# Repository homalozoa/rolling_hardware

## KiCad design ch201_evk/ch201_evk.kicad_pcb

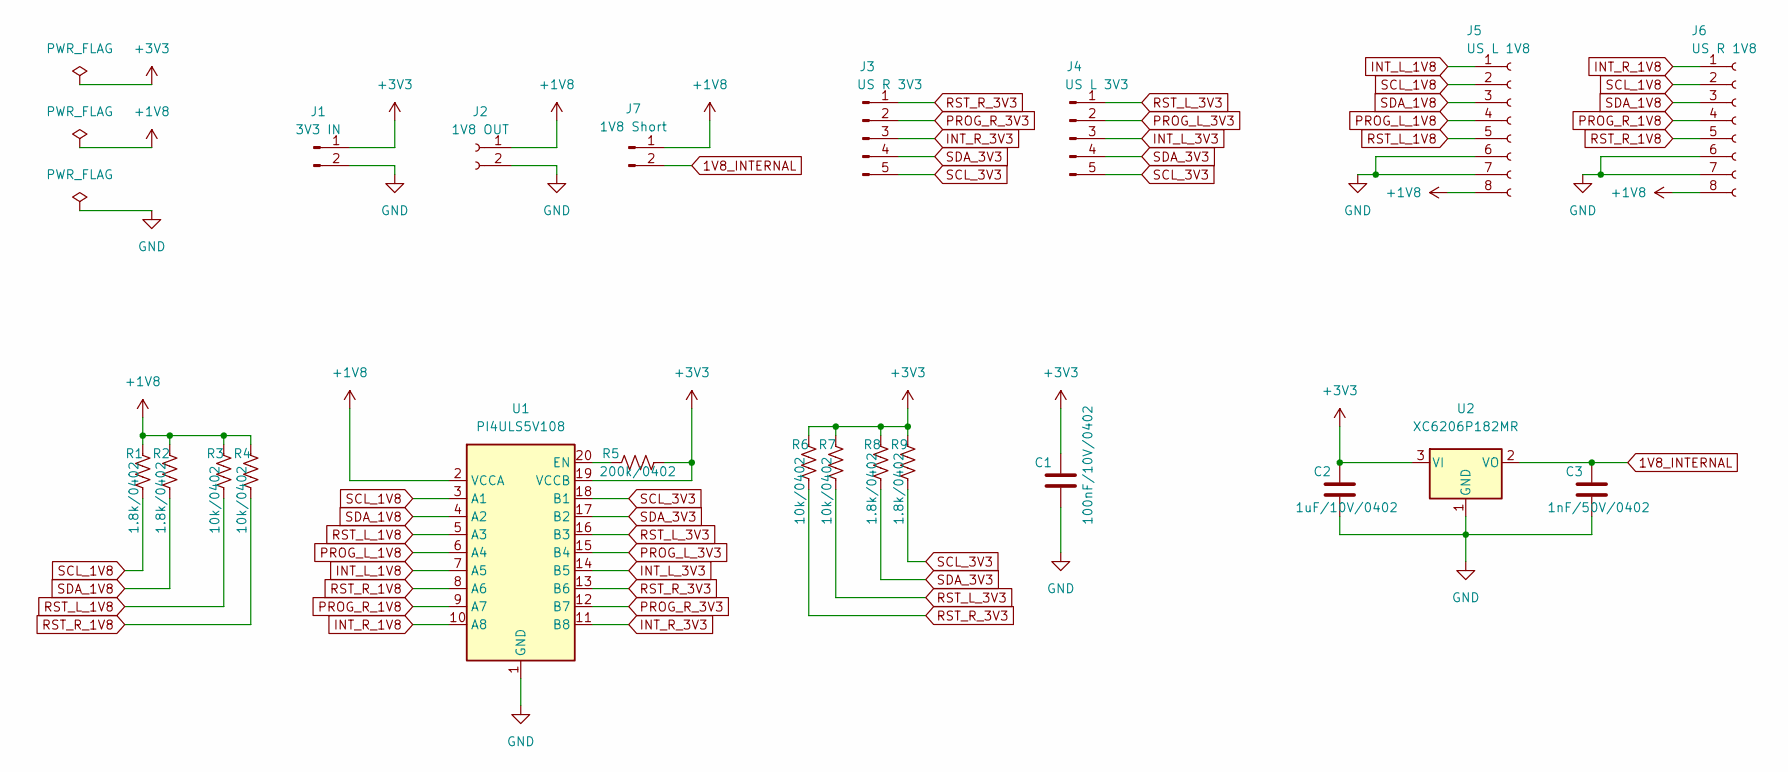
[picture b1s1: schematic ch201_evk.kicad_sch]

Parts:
C1: 100nF/10V/0402; C_0402_1005Metric
C2: 1uF/10V/0402; C_0402_1005Metric
C3: 1nF/50V/0402; C_0402_1005Metric
J1: 3V3 IN; PinHeader_1x02_P2.54mm_Vertical
J2: 1V8 OUT; PinHeader_1x02_P2.54mm_Vertical
J3: US R 3V3; PinHeader_1x05_P2.54mm_Vertical
J4: US L 3V3; PinHeader_1x05_P2.54mm_Vertical
J5: US L 1V8; MOLEX_5034800800
J6: US R 1V8; MOLEX_5034800800
J7: 1V8 Short; PinHeader_1x02_P2.54mm_Vertical
R1, R2, R8, R9: 1.8k/0402; R_0402_1005Metric
R3, R4, R6, R7: 10k/0402; R_0402_1005Metric
R5: 200k/0402; R_0402_1005Metric
U1: PI4ULS5V108; DHVQFN20_SOT764-1
U2: XC6206P182MR; SOT-23

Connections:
1V8_INTERNAL: C3.1, J7.2, U2.2 (VO)
+1V8: J2.1, J5.8, J6.8, J7.1, R1.1, R2.1, R3.1, R4.1, U1.2 (VCCA); also elsewhere on the board
+3V3: C1.1, C2.1, J1.1, R5.2, R6.1, R7.1, R8.1, R9.1, U1.19 (VCCB), U2.3 (VI)
GND: C1.2, C2.2, C3.2, J1.2, J2.2, J5.6, J5.7, J6.6, J6.7, U1.1 (GND), U2.1 (GND); also elsewhere on the board
INT_L_1V8: J5.1, U1.7 (A5); also elsewhere on the board
INT_L_3V3: J4.3, U1.14 (B5)
INT_R_1V8: J6.1, U1.10 (A8); also elsewhere on the board
INT_R_3V3: J3.3, U1.11 (B8)
unnamed: R5.1, U1.20 (EN)
PROG_L_1V8: J5.4, U1.6 (A4); also elsewhere on the board
PROG_L_3V3: J4.2, U1.15 (B4)
PROG_R_1V8: J6.4, U1.9 (A7); also elsewhere on the board
PROG_R_3V3: J3.2, U1.12 (B7)
RST_L_1V8: J5.5, R3.2, U1.5 (A3); also elsewhere on the board
RST_L_3V3: J4.1, R7.2, U1.16 (B3)
RST_R_1V8: J6.5, R4.2, U1.8 (A6); also elsewhere on the board
RST_R_3V3: J3.1, R6.2, U1.13 (B6)
SCL_1V8: J5.2, J6.2, R1.2, U1.3 (A1); also elsewhere on the board
SCL_3V3: J3.5, J4.5, R9.2, U1.18 (B1)
SDA_1V8: J5.3, J6.3, R2.2, U1.4 (A2); also elsewhere on the board
SDA_3V3: J3.4, J4.4, R8.2, U1.17 (B2)

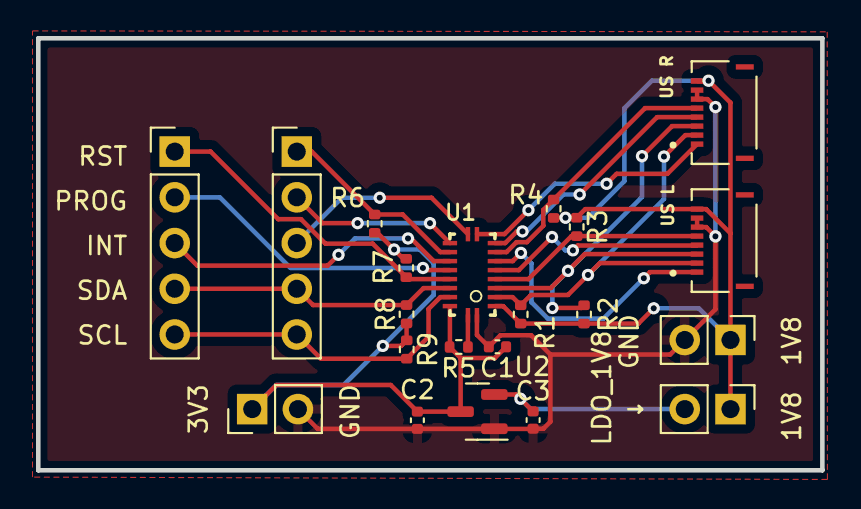
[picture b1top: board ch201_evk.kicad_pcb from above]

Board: 2 copper layers, 43.6 x 24.0 mm, 21 parts (0 on the bottom side), 21 nets.

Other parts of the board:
US L: US L 1V8; MOLEX_5034800800
US R: US R 1V8; MOLEX_5034800800

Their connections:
+1V8: US L.8, US R.8; also elsewhere on the board
GND: US L.6, US L.7, US R.6, US R.7; also elsewhere on the board
INT_L_1V8: US L.1; also elsewhere on the board
INT_R_1V8: US R.1; also elsewhere on the board
PROG_L_1V8: US L.4; also elsewhere on the board
PROG_R_1V8: US R.4; also elsewhere on the board
RST_L_1V8: US L.5; also elsewhere on the board
RST_R_1V8: US R.5; also elsewhere on the board
SCL_1V8: US L.2, US R.2; also elsewhere on the board
SDA_1V8: US L.3, US R.3; also elsewhere on the board

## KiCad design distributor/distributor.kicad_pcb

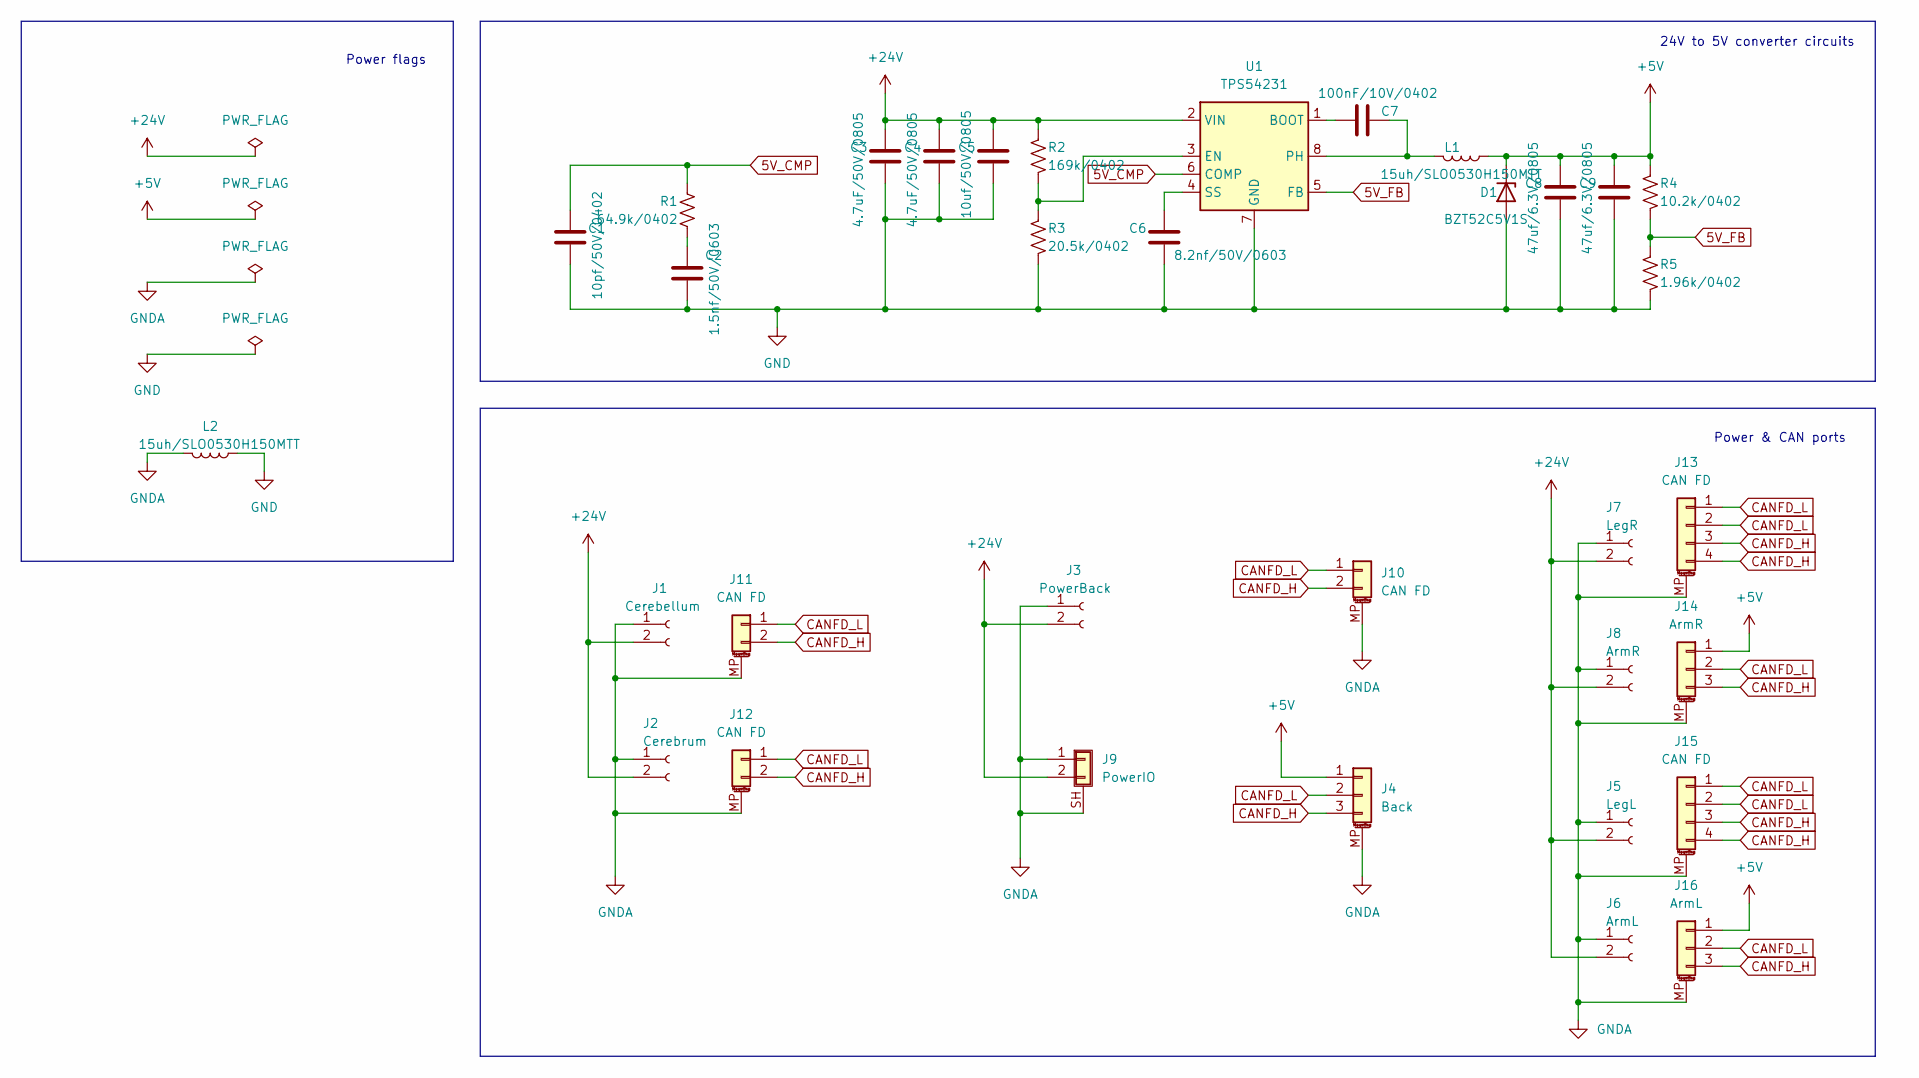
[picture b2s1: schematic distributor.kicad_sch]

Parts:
C1: 10pf/50V/0402; C_0402_1005Metric
C2: 1.5nf/50V/0603; C_0603_1608Metric
C3, C4: 4.7uF/50V/0805; C_0805_2012Metric
C5: 10uf/50V/0805; C_0805_2012Metric
C6: 8.2nf/50V/0603; C_0603_1608Metric
C7: 100nF/10V/0402; C_0402_1005Metric
C8, C9: 47uf/6.3V/0805; C_0805_2012Metric
D1: BZT52C5V1S; D_SOD-323
J1: Cerebellum; AMASS_XT30PW-M_1x02_P2.50mm_Horizontal
J2: Cerebrum; AMASS_XT30PW-M_1x02_P2.50mm_Horizontal
J3: PowerBack; AMASS_XT30PW-M_1x02_P2.50mm_Horizontal
J4: Back; JST_GH_SM03B-GHS-TB_1x03-1MP_P1.25mm_Horizontal
J5: LegL; AMASS_XT30PW-M_1x02_P2.50mm_Horizontal
J6: ArmL; AMASS_XT30PW-M_1x02_P2.50mm_Horizontal
J7: LegR; AMASS_XT30PW-M_1x02_P2.50mm_Horizontal
J8: ArmR; AMASS_XT30PW-M_1x02_P2.50mm_Horizontal
J9: PowerIO; AMASS_XT60PW-F
J10, J11, J12: CAN FD; JST_GH_SM02B-GHS-TB_1x02-1MP_P1.25mm_Horizontal
J13, J15: CAN FD; JST_GH_SM04B-GHS-TB_1x04-1MP_P1.25mm_Horizontal
J14: ArmR; JST_GH_SM03B-GHS-TB_1x03-1MP_P1.25mm_Horizontal
J16: ArmL; JST_GH_SM03B-GHS-TB_1x03-1MP_P1.25mm_Horizontal
L1, L2: 15uh/SLO0530H150MTT; L_Sunlord_MWSA0518_5.4x5.2mm
R1: 64.9k/0402; R_0402_1005Metric
R2: 169k/0402; R_0402_1005Metric
R3: 20.5k/0402; R_0402_1005Metric
R4: 10.2k/0402; R_0402_1005Metric
R5: 1.96k/0402; R_0402_1005Metric
U1: TPS54231; SOIC-8_3.9x4.9mm_P1.27mm

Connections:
5V_CMP: C1.1, R1.1, U1.6 (COMP)
5V_FB: R4.2, R5.1, U1.5 (FB)
+5V: C8.1, C9.1, D1.1 (K), J4.1, J14.1, J16.1, L1.1, R4.1
+24V: C3.1, C4.1, C5.1, J1.2, J2.2, J3.2, J5.2, J6.2, J7.2, J8.2, J9.2, R2.1, U1.2 (VIN)
CANFD_H: J4.3, J10.2, J11.2, J12.2, J13.3, J13.4, J14.3, J15.3, J15.4, J16.3
CANFD_L: J4.2, J10.1, J11.1, J12.1, J13.1, J13.2, J14.2, J15.1, J15.2, J16.2
GND: C1.2, C2.2, C3.2, C4.2, C5.2, C6.2, C8.2, C9.2, D1.2 (A), L2.1, R3.2, R5.2, U1.7 (GND)
GNDA: J1.1, J2.1, J3.1, J4.MP (MountPin), J5.1, J6.1, J7.1, J8.1, J9.1, J9.SH (Shield), J10.MP (MountPin), J11.MP (MountPin), J12.MP (MountPin), J13.MP (MountPin), J14.MP (MountPin), J15.MP (MountPin), J16.MP (MountPin), L2.2; also elsewhere on the board
unnamed: C2.1, R1.2
unnamed: C6.1, U1.4 (SS)
unnamed: C7.1, L1.2, U1.8 (PH)
unnamed: C7.2, U1.1 (BOOT)
unnamed: R2.2, R3.1, U1.3 (EN)

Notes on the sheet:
24V to 5V converter circuits
Power flags
Power & CAN ports

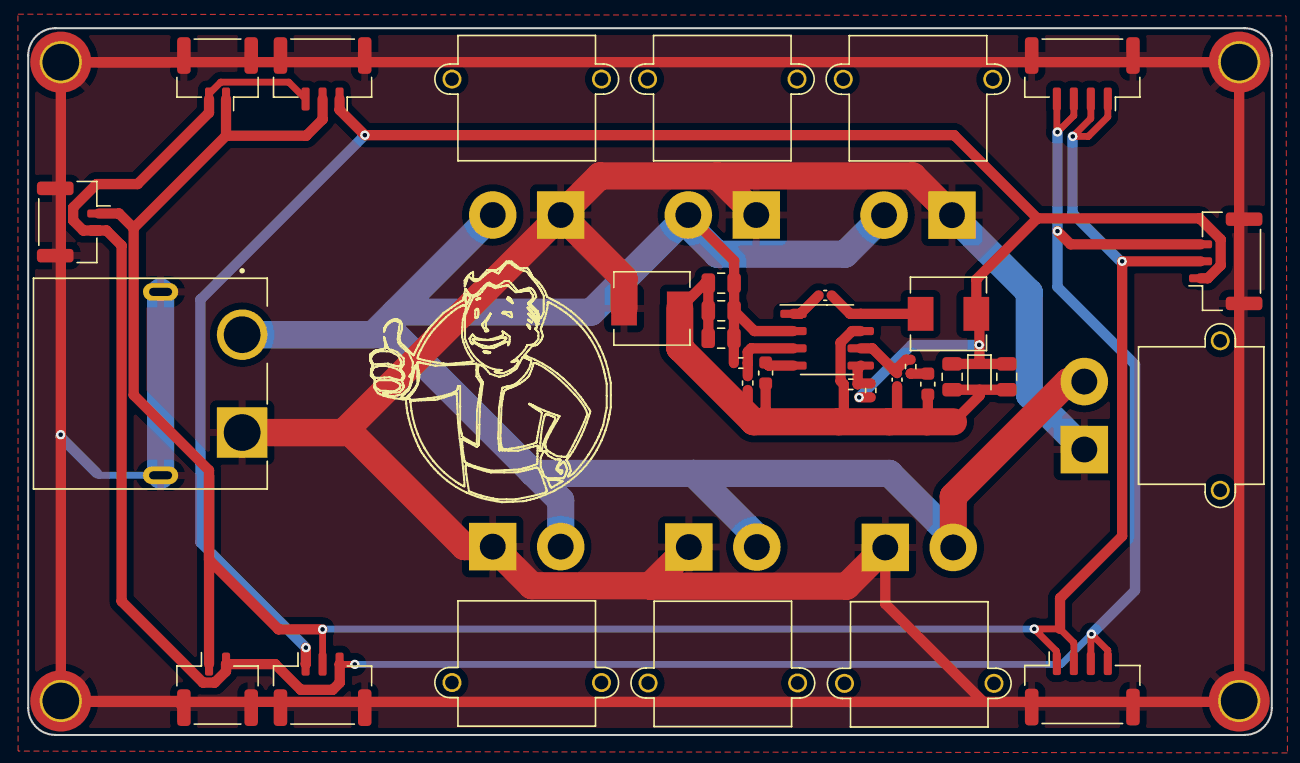
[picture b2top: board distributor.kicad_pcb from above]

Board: 2 copper layers, 91.5 x 52.0 mm, 38 parts (0 on the bottom side), 13 nets.

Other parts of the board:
Mount2, Mount3, Mount4, Mount4#2: MountingHole_2.7mm_M2.5_ISO7380_Pad_TopBottom

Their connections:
GNDA: Mount2.1, Mount3.1, Mount4.1, Mount4#2.1; also elsewhere on the board

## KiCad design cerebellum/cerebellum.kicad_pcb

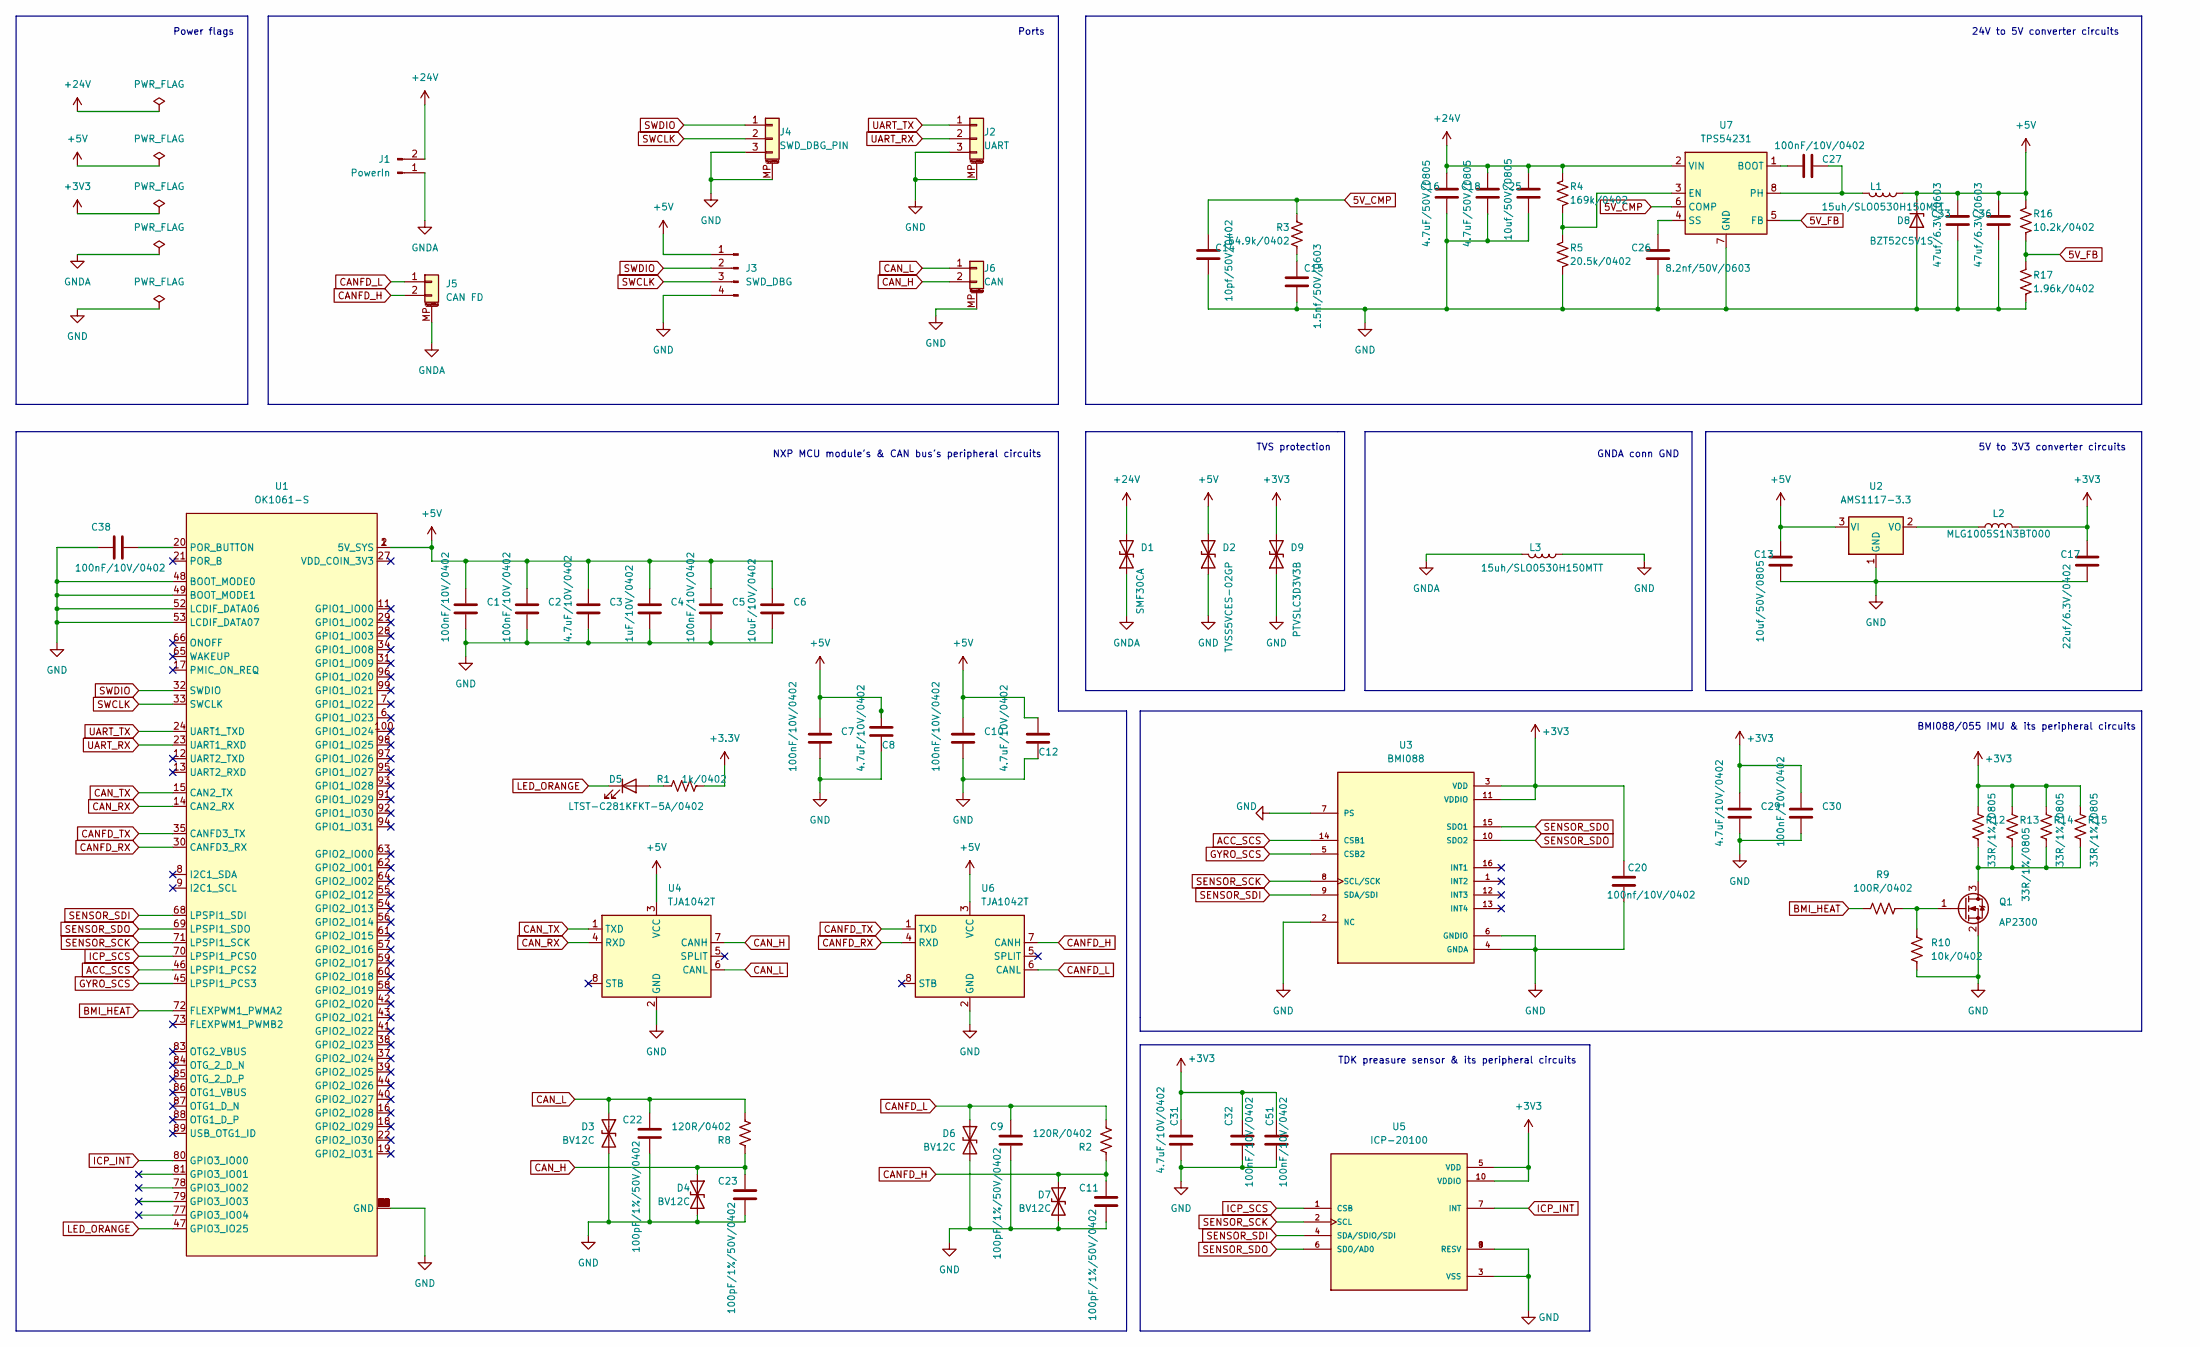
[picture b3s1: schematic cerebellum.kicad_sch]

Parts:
C1, C2, C5, C7, C10, C27, C30, C32, C38, C51: 100nF/10V/0402; C_0402_1005Metric
C3, C8, C12, C29, C31: 4.7uF/10V/0402; C_0402_1005Metric
C4: 1uF/10V/0402; C_0402_1005Metric
C6: 10uF/10V/0402; C_0402_1005Metric
C9, C11, C22, C23: 100pF/1%/50V/0402; C_0402_1005Metric
C13, C25: 10uf/50V/0805; C_0805_2012Metric
C14: 10pf/50V/0402; C_0402_1005Metric
C15: 1.5nf/50V/0603; C_0603_1608Metric
C16, C18: 4.7uF/50V/0805; C_0805_2012Metric
C17: 22uf/6.3V/0402; C_0402_1005Metric
C20: 100nf/10V/0402; C_0402_1005Metric
C26: 8.2nf/50V/0603; C_0603_1608Metric
C33, C36: 47uf/6.3V/0603; C_0603_1608Metric
D1: SMF30CA; D_SOD-123
D2: TVSS5VCES-02GP; D_SOD-523
D3, D4, D6, D7: BV12C; D_SOD-323
D5: LTST-C281KFKT-5A/0402; LED_0402_1005Metric
D8: BZT52C5V1S; D_SOD-323
D9: PTVSLC3D3V3B; D_SOD-323
J1: PowerIn; AMASS_XT30PW-M_1x02_P2.50mm_Horizontal
J2: UART; JST_GH_SM03B-GHS-TB_1x03-1MP_P1.25mm_Horizontal
J3: SWD_DBG; PinHeader_1x04_P1.27mm_Vertical
J4: SWD_DBG_PIN; JST_GH_SM03B-GHS-TB_1x03-1MP_P1.25mm_Horizontal
J5: CAN FD; JST_GH_SM02B-GHS-TB_1x02-1MP_P1.25mm_Horizontal
J6: CAN; JST_GH_SM02B-GHS-TB_1x02-1MP_P1.25mm_Horizontal
L1, L3: 15uh/SLO0530H150MTT; L_Sunlord_MWSA0518_5.4x5.2mm
L2: MLG1005S1N3BT000; L_0402_1005Metric
Q1: AP2300; SOT-23
R1: 1k/0402; R_0402_1005Metric
R2, R8: 120R/0402; R_0402_1005Metric
R3: 64.9k/0402; R_0402_1005Metric
R4: 169k/0402; R_0402_1005Metric
R5: 20.5k/0402; R_0402_1005Metric
R9: 100R/0402; R_0402_1005Metric
R10: 10k/0402; R_0402_1005Metric
R12, R13, R14, R15: 33R/1%/0805; R_0805_2012Metric
R16: 10.2k/0402; R_0402_1005Metric
R17: 1.96k/0402; R_0402_1005Metric
U1: OK1061-S; OK1061-S-100
U2: AMS1117-3.3; SOT-223-3_TabPin2
U3: BMI088; PQFN50P450X300X100-16N
U4, U6: TJA1042T; SOIC-8_3.9x4.9mm_P1.27mm
U5: ICP-20100; PQFN50P200X200X85-10N; PARTREV 1.1
U7: TPS54231; SOIC-8_3.9x4.9mm_P1.27mm

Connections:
5V_CMP: C14.1, R3.1, U7.6 (COMP)
5V_FB: R16.2, R17.1, U7.5 (FB)
+5V: C1.1, C2.1, C3.1, C4.1, C5.1, C6.1, C7.1, C8.1, C10.1, C12.1, C13.1, C33.1, C36.1, D2.2 (A2), D8.1 (K), J3.1, L1.1, R16.1, U1.1 (5V_SYS), U1.2 (5V_SYS), U2.3 (VI), U4.3 (VCC), U6.3 (VCC)
+24V: C16.1, C18.1, C25.1, D1.2 (A2), J1.2, R4.1, U7.2 (VIN)
ACC_SCS: U1.46 (LPSPI1_PCS2), U3.14 (CSB1)
BMI_HEAT: R9.2, U1.72 (FLEXPWM1_PWMA2)
CANFD_H: C11.2, D7.1 (A1), J5.2, R2.1, U6.7 (CANH)
CANFD_L: C9.2, D6.1 (A1), J5.1, R2.2, U6.6 (CANL)
CANFD_RX: U1.30 (CANFD3_RX), U6.4 (RXD)
CANFD_TX: U1.35 (CANFD3_TX), U6.1 (TXD)
CAN_H: C23.2, D4.1 (A1), J6.2, R8.1, U4.7 (CANH)
CAN_L: C22.2, D3.1 (A1), J6.1, R8.2, U4.6 (CANL)
CAN_RX: U1.14 (CAN2_RX), U4.4 (RXD)
CAN_TX: U1.15 (CAN2_TX), U4.1 (TXD)
GND: C1.2, C2.2, C3.2, C4.2, C5.2, C6.2, C7.2, C8.2, C9.1, C10.2, C11.1, C12.2, C13.2, C14.2, C15.2, C16.2, C17.2, C18.2, C20.2, C22.1, C23.1, C25.2, C26.2, C29.2, C30.2, C31.2, C32.2, C33.2, C36.2, C38.1, C51.2, D2.1 (A1), D3.2 (A2), D4.2 (A2), D6.2 (A2), D7.2 (A2), D8.2 (A), D9.1 (A1), J2.3, J2.MP (MountPin), J3.4, J4.3, J4.MP (MountPin), J6.MP (MountPin), L3.1, Q1.2 (S), R5.2, R10.2, R17.2, U1.3 (GND), U1.4 (GND), U1.5 (GND), U1.10 (GND), U1.25 (GND), U1.26 (GND), U1.36 (GND), U1.48 (BOOT_MODE0), U1.49 (BOOT_MODE1), U1.50 (GND), U1.51 (GND), U1.52 (LCDIF_DATA06), U1.53 (LCDIF_DATA07), U1.67 (GND), U1.74 (GND), U1.75 (GND), U1.76 (GND), U1.82 (GND), U1.90 (GND), U2.1 (GND), U3.2 (NC), U3.4 (GNDA), U3.6 (GNDIO), U3.7 (PS), U4.2 (GND), U5.3 (VSS), U5.8 (RESV), U5.9 (RESV), U6.2 (GND), U7.7 (GND)
GNDA: D1.1 (A1), J1.1, J5.MP (MountPin), L3.2; also elsewhere on the board
GYRO_SCS: U1.45 (LPSPI1_PCS3), U3.5 (CSB2)
ICP_INT: U1.80 (GPIO3_IO00), U5.7 (INT)
ICP_SCS: U1.70 (LPSPI1_PCS0), U5.1 (CSB)
LED_ORANGE: D5.1 (K), U1.47 (GPIO3_IO25)
unnamed: C15.1, R3.2
unnamed: C26.1, U7.4 (SS)
unnamed: C27.1, L1.2, U7.8 (PH)
unnamed: C27.2, U7.1 (BOOT)
unnamed: C38.2, U1.20 (POR_BUTTON)
unnamed: D5.2 (A), R1.1
unnamed: L2.1, U2.2 (VO)
unnamed: Q1.1 (G), R9.1, R10.1
unnamed: Q1.3 (D), R12.2, R13.2, R14.2, R15.2
unnamed: R4.2, R5.1, U7.3 (EN)
SENSOR_SCK: U1.71 (LPSPI1_SCK), U3.8 (SCL/SCK), U5.2 (SCL)
SENSOR_SDI: U1.68 (LPSPI1_SDI), U3.9 (SDA/SDI), U5.4 (SDA/SDIO/SDI)
SENSOR_SDO: U1.69 (LPSPI1_SDO), U3.10 (SDO2), U3.15 (SDO1), U5.6 (SDO/AD0)
SWCLK: J3.3, J4.2, U1.33 (SWCLK)
SWDIO: J3.2, J4.1, U1.32 (SWDIO)
UART_RX: J2.2, U1.23 (UART1_RXD)
UART_TX: J2.1, U1.24 (UART1_TXD)

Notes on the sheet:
BMI088/055 IMU & its peripheral circuits
TDK preasure sensor & its peripheral circuits
Ports
GNDA conn GND
5V to 3V3 converter circuits
NXP MCU module's & CAN bus's peripheral circuits
TVS protection
Power flags
24V to 5V converter circuits

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
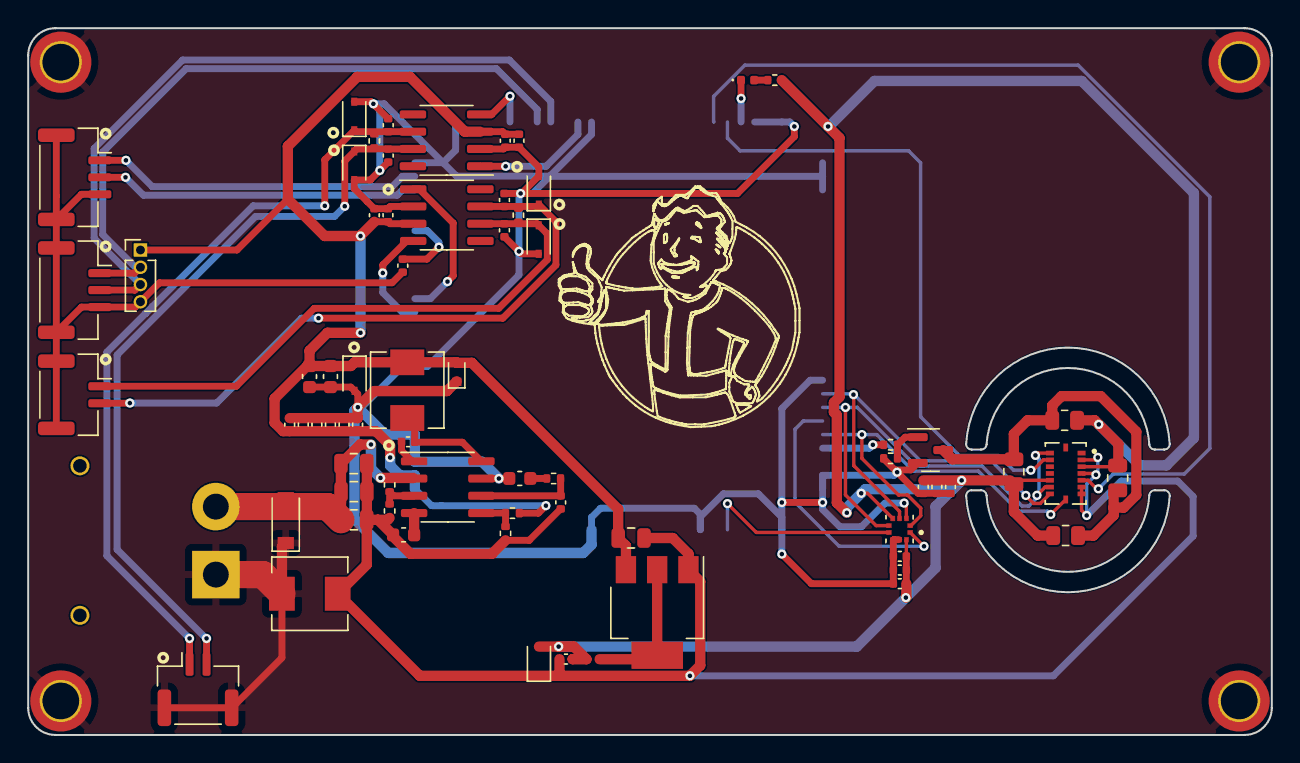
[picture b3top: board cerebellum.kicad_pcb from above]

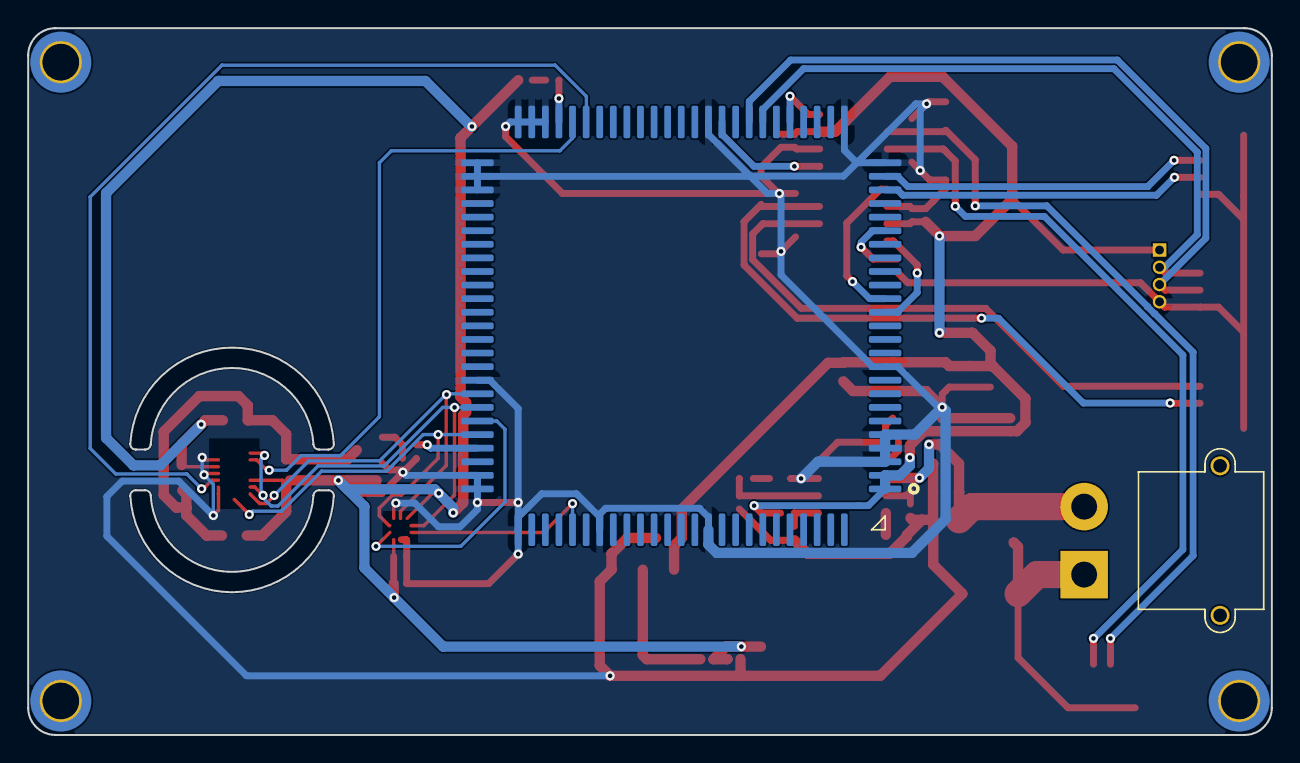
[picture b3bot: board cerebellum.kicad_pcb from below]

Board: 2 copper layers, 91.5 x 52.0 mm, 76 parts (2 on the bottom side), 38 nets.

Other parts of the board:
Mount1, Mount2, Mount3, Mount4: MountingHole_2.7mm_M2.5_ISO7380_Pad_TopBottom

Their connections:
GNDA: Mount1.1, Mount2.1, Mount3.1, Mount4.1; also elsewhere on the board

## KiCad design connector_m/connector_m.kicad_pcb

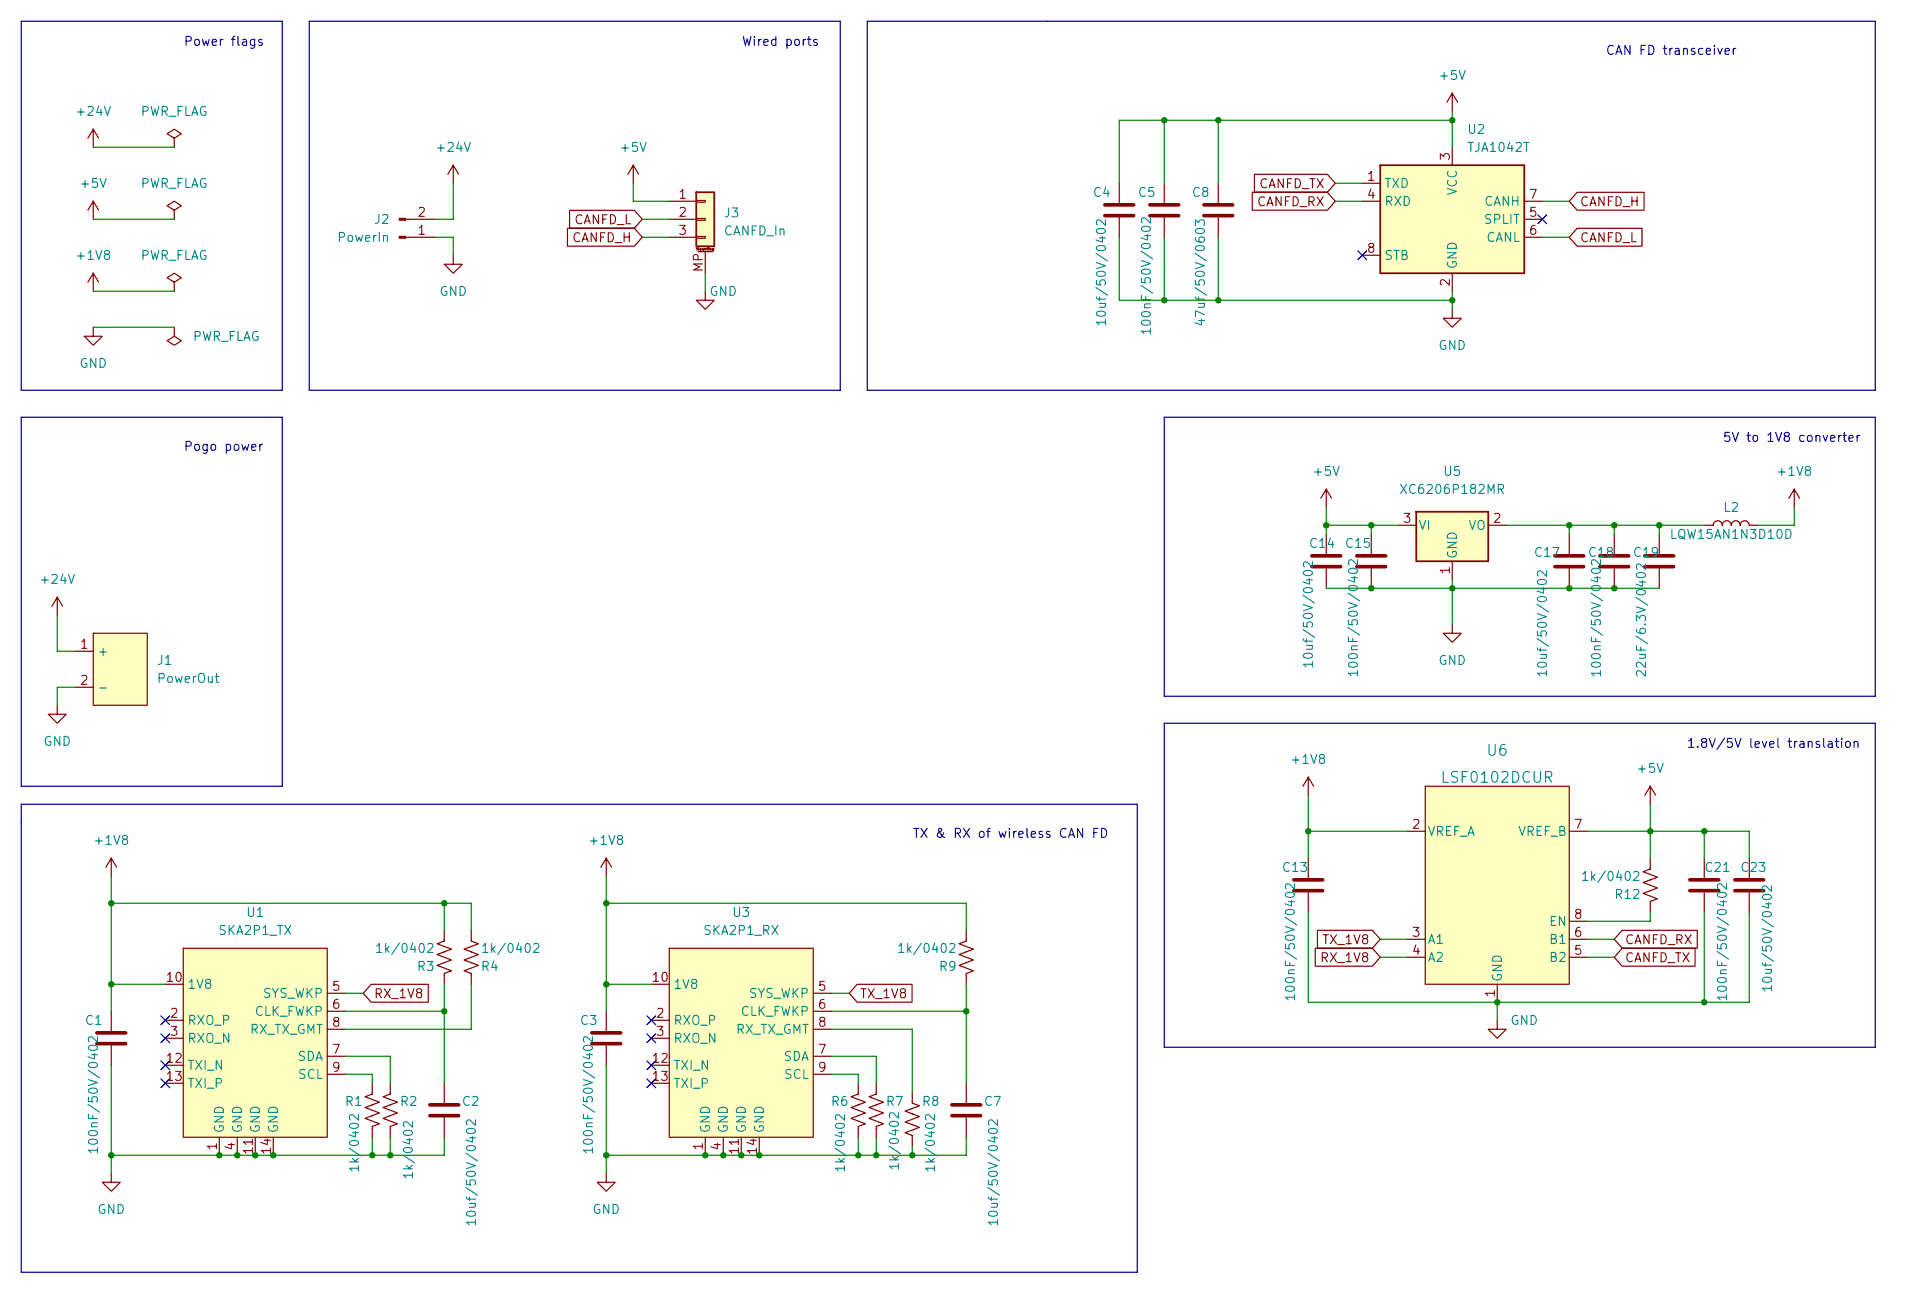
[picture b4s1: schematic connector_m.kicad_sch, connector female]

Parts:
C1, C3, C5, C13, C15, C18, C21: 100nF/50V/0402; C_0402_1005Metric
C2, C4, C7, C14, C17, C23: 10uf/50V/0402; C_0402_1005Metric
C8: 47uf/50V/0603; C_0603_1608Metric
C19: 22uF/6.3V/0402; C_0402_1005Metric
J1: PowerOut; POGOPIN-E21160-ASB-2PIN
J2: PowerIn; AMASS_XT30U-M_1x02_P5.0mm_Vertical
J3: CANFD_In; JST_GH_BM03B-GHS-TBT_1x03-1MP_P1.25mm_Vertical
L2: LQW15AN1N3D10D; L_0402_1005Metric
R1, R2, R3, R4, R6, R7, R8, R9, R12: 1k/0402; R_0402_1005Metric
U1: SKA2P1_TX; SKA2P1
U2: TJA1042T; SOIC-8_3.9x4.9mm_P1.27mm
U3: SKA2P1_RX; SKA2P1
U5: XC6206P182MR; SOT-23
U6: LSF0102DCUR; VSSOP-8_2.3x2mm_P0.5mm

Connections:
+1V8: C1.1, C3.1, C13.1, L2.2, R3.2, R4.2, R9.2, U1.10 (1V8), U3.10 (1V8), U6.2 (VREF_A)
+5V: C4.1, C5.1, C8.1, C14.1, C15.1, C21.1, C23.1, J3.1, R12.2, U2.3 (VCC), U5.3 (VI), U6.7 (VREF_B)
+24V: J1.1 (+), J2.2
CANFD_H: J3.3, U2.7 (CANH)
CANFD_L: J3.2, U2.6 (CANL)
CANFD_RX: U2.4 (RXD), U6.6 (B1)
CANFD_TX: U2.1 (TXD), U6.5 (B2)
GND: C1.2, C2.2, C3.2, C4.2, C5.2, C7.2, C8.2, C13.2, C14.2, C15.2, C17.2, C18.2, C19.2, C21.2, C23.2, J1.2 (-), J2.1, J3.MP (MountPin), R1.1, R2.2, R6.1, R7.2, R8.1, U1.1 (GND), U1.4 (GND), U1.11 (GND), U1.14 (GND), U2.2 (GND), U3.1 (GND), U3.4 (GND), U3.11 (GND), U3.14 (GND), U5.1 (GND), U6.1 (GND)
unnamed: C2.1, R3.1, U1.6 (CLK_FWKP)
unnamed: C7.1, R9.1, U3.6 (CLK_FWKP)
unnamed: C17.1, C18.1, C19.1, L2.1, U5.2 (VO)
unnamed: R1.2, U1.9 (SCL)
unnamed: R2.1, U1.7 (SDA)
unnamed: R4.1, U1.8 (RX_TX_GMT)
unnamed: R6.2, U3.9 (SCL)
unnamed: R7.1, U3.7 (SDA)
unnamed: R8.2, U3.8 (RX_TX_GMT)
unnamed: R12.1, U6.8 (EN)
RX_1V8: U1.5 (SYS_WKP), U6.4 (A2)
TX_1V8: U3.5 (SYS_WKP), U6.3 (A1)

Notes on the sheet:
Pogo power
1.8V/5V level translation
Power flags
CAN FD transceiver
TX & RX of wireless CAN FD
Wired ports
5V to 1V8 converter

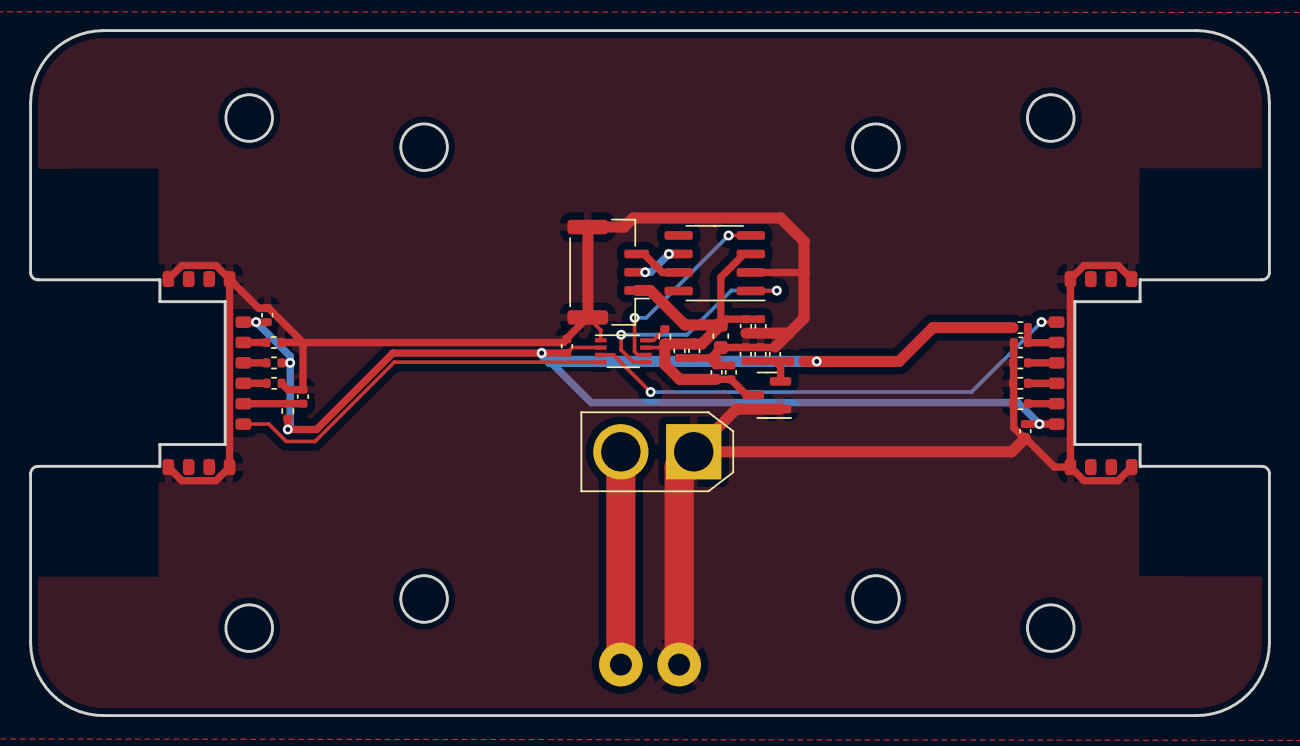
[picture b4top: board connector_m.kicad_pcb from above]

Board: 2 copper layers, 85.0 x 47.0 mm, 33 parts (1 on the bottom side), 20 nets.

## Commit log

2022-08-21 [New] Add prj cerebellum & limbic_cm4 & limbic_x3m
2022-08-21 [New] Add comments to PCB board & Fix unconnected
    1. Add date & signature to PCB board
    2. Fix an unconnected wire
2022-08-21 [New] Update executor sch
2022-08-21 [Modify] Change footprints for manufature
2022-08-21 [New] Add rpi_cm4 to lib
2022-08-21 [New] Add executor pcb prj
2022-08-21 [New] complete executor PCB layout
2022-08-21 [New] Add XT30PW(2+2) & connector
2022-08-21 [Fix] Fix library path
2022-08-21 [New] Add output dir to gitignore
2022-08-21 [Fix] Move Acc sensor to avoid mechanical stress
2022-08-21 [New] Complete executor ver 0.1
2022-08-21 [New] Add temp files to gitignore
2022-08-21 [Fix] Fix tcan4550 spi wrong connection
2022-08-21 [New] Complete executor sch
2022-08-21 [New] Add UFBGA25 to libraries fp
2022-08-21 [Fix] Exchange resistors in IMU heat circuit
2022-08-21 [New] Add flash_esp
2022-08-21 [New] Fix position for executor
2022-08-21 [New] Add XT60PW-M/F to library
2022-08-21 [New] Add typec to lib
2022-08-21 [New] Add 4pin for fast flash
2022-08-21 [New] Add heart
2022-08-21 [New] Add ioc to executor
2022-08-21 [New] Add tvs to cerebellum
2022-08-21 [New] Add JST & Molex to libraries
2022-08-21 [New] Add bmi&icp&tcan to cerebellum
2022-08-21 [New] Complete PCB of flasher_esp
2022-08-21 [Fix] Fix stlink route to straight
2022-08-21 [New] Add Espressif library
2022-08-21 [New] NC serveral pins of CM4 & Add uPD720201
2022-08-21 [New] Add folder "appendix" & st60_test
2022-08-21 [New] Add eth transmit to lib
2022-08-21 [New] Add .kicad_sch-bak to .gitignore
2022-08-21 [Fix] Fix st60_test_a mountinghole position
2022-08-21 [Modify] Remove limbic_cm4
2022-08-21 [New] Add cm4 to cerebellum
2022-08-21 [New] Almost complete heart board
2022-08-21 [Modify] Tune length of CAN bus wires
2022-08-21 [Complete cerebellum schematic
    * add gd32f405vghx to library
2022-08-21 [New] Add DF40C-100DS to lib
2022-08-21 [New] Add xHCI USB 3.0 controller to lib
2022-08-21 [New] Complete heart board
2022-08-21 [New] Add XT30PB(2+2) to library
2022-08-21 [New] Add limbic_cm4 for temporary backup
2022-08-21 [Modify] Refactor cerebellum for replacing xt30/60s
2022-08-21 [New] Add some capacities to cerebellum
2022-08-21 [Fix] Fix package of diode in cerebellum
2022-08-21 [New] Complete cerebellum
    * Refactor cerebellum, now cerebellum includes features of heart &
    cerebellum
2022-08-21 [New] Add USB ports to cerebellum
2022-08-21 [New] Add 1.05 LDO to cerebellum
2022-08-21 [New] Change mounting hole in cerebellum
2022-08-21 [Fix] Replace dc-dc module to tps & fix xt30-2+2 position
2022-08-21 [New] Add USB switches & flash to cerebellum
2022-08-21 [New] Add USB devices to lib
2022-08-21 [New] Add USB Type-C ports to library
2022-08-21 [New] Refactoring placement & routing of cerebellum
2022-08-21 [Fix] Correct pin assignment of AMASS XT60 M&F
    Pin 1 to GND
    Pin 2 to PWR
2022-08-21 [New] Add OK1061-S to library
2022-08-21 [New] Complete new cerebellum
    1. it's based on NXP MIMXRT1061CVL5A
    2. it supports xt30(2+2)x7 output, xt60x1 input
    3. it supports CAN FD & CAN 2.0
2022-08-21 [Version] TestVersionAlpha
    1. Remove limbic_cm4/x3m projects
    2. Move flasher_esp into appendix
    3. Remove heart board
    4. Add rt1010 MCU to library
2022-08-21 [Fix] Add lost dxf of pipboy
2022-08-21 [Update] Redesign PCB layout of cerebellum
    1. Remove duplicated xt30(2+2) ports
    2. Redesign PCB layout for new cerebellum
    3. Add lines in cerebellum schematic to split different functional area.
2022-08-21 [New] Rerouting cerebellum & add dxfs
    1. Rerouting cerebellum for new design. There are only two layers in this design.
    2. Add common board DXF file and cerebellum DXF file. Also I added their source file for convenient modification in the future.
2022-08-21 [Modify] Remove XT30(2+2), replaced by XT30 + GH 2pins
    XT30(2+2) is not as robust as expected, so I replace all ports by XT30 and JST GH 1.25mm 2pin.
2022-08-21 [Modify] Optimize OK1601-S symbol
2022-08-21 [Modify] Change FP of battery power input & SWD
    1. Change battery input port to XT60 M vertical.
    2. Change SWD port to Horizontal.
2022-08-21 [New] Add heart schematic & update lib
    1. New board named "heart". It controls all power input and output. Including PD charging for 6S LiPo battery. Now it is designed for 5000mah capacity. The capacity could be changed by replacing resi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
    2. As description in 1. I added some new symbols in Rolling_Custom library. Like IP2368, a chip for PD charging.
2022-08-21 [New] Complete Heart board v2.0
    1. There are two XT60 ports on heart board, one for power input, one for power output.
    2. There is a 4pin GH 1.25 port, designed for CAN FD(1.CAN_H, 2.CAN_H, 3.CAN_L, 4.CAN_L)
    3. USB Type C port is designed for PD charging.
    4. Also there is a SWD port for flashing and debugging.
2022-08-21 [New] Add distributor version 1.0
    *. Distributor is designed for Power & CAN FD distribution.
2022-08-21 [Fix] Move components to avoid collisions
2022-08-21 [Fix] Complete resistor value of 24Vto5V regulator
2022-08-21 [New] Add SKA2P1 footprint
2022-08-21 [Modify] Change XT30(2+2) input to XT30 + GH 2pin
    As commit before.
2022-08-21 [New] Replace TI's solution with TMC's in executor prj
    1. DRV8323 --> TMC6200
    2. GD32F303 --> TMC4671 + GD32C103
    3. TCAN4550 --> GD32C103
2022-08-21 [Fix] Fix XT60 layout & Change CAN ports
    1. It seems 2pin is enough for CAN FD inside the body.
    2. Fix XT60 layout.
2022-08-21 [New] Complete sch & pcb of connector_f
    1. connector female is a board designed for wireless connector. Power is supplied by pogo pins, signals are supplied by ST60s.
2022-08-21 [Modify] Complete descriptions in schematics
    including cerebellum and heart.
2022-08-21 [Fix] Remove duplicated courtyard
2022-08-21 [New] Add TMC chips & conn to library
    1. Add TMC4671, a FOC ASIC
    2. Add TMC6200, a MOSFET driver
    3. Add FH34SRJ-6J footprint
2022-08-21 [Modify] Pinned lib in prj cerebellum
2022-08-21 [New] Add 24V to 5V converter to distributor
2022-08-21 [New] Complete PCB layout of executor v2.0
2022-08-21 [Modify] Remove connector prj
2022-08-21 [New] Add connector m
2022-08-21 [New] Add 3D models configuration for components
2022-08-21 [New] Add connector
2022-08-21 [New] Release all board 3D models
    * All files are in folder "steps".
2022-08-21 [Fix] Correct capacities in 24Vto5V converter
2022-08-21 [Modify] Update new steps
2022-08-21 [Fix] Correct capacities in 24Vto5V again.
2022-08-21 [Fix] Correct mounting hole positions
2022-08-21 [Modify] Change CAN ports sequence
    2pin: 1-CAN_L, 2-CAN_H
    3pin: 1-5V, 2-CAN_L, 3-CAN_H
    4pin: 1,2-CAN_L, 3,4-CAN_H
2022-08-21 [Fix] Correct distributor layout
2022-08-21 [Modify] Change edge.cut layer of SKA2P1
    * Now you must route edges when using SKA2P1 in designs
2022-08-21 [Fix] Correct female xt60 fp
2022-08-21 [New] Re-layout PCB connector male
2022-08-21 [New] Add *jlcpcb to gitignore
2022-08-21 [Fix] Connect mounting hole to GNDA
2022-08-21 [Modify] Change pogopin to Taobao version
2022-08-21 [Modify] Replace DCDC(24to3V3) to LDO(5to3V3)
2022-08-21 [Modify] Update lib in connector_m
2022-08-21 [Modify] Change pressure sensor to MPL3115A2R1
2022-08-21 [Fix] Manufacture modification
2023-03-19 feat:lib add PI4ULS5V108 sym & fp && molex 50348 fp
2023-03-19 feat:prj add ch201_evk

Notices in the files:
parts and their libraries:
Copyright 2021 Accelerated Designs. All rights reserved.
